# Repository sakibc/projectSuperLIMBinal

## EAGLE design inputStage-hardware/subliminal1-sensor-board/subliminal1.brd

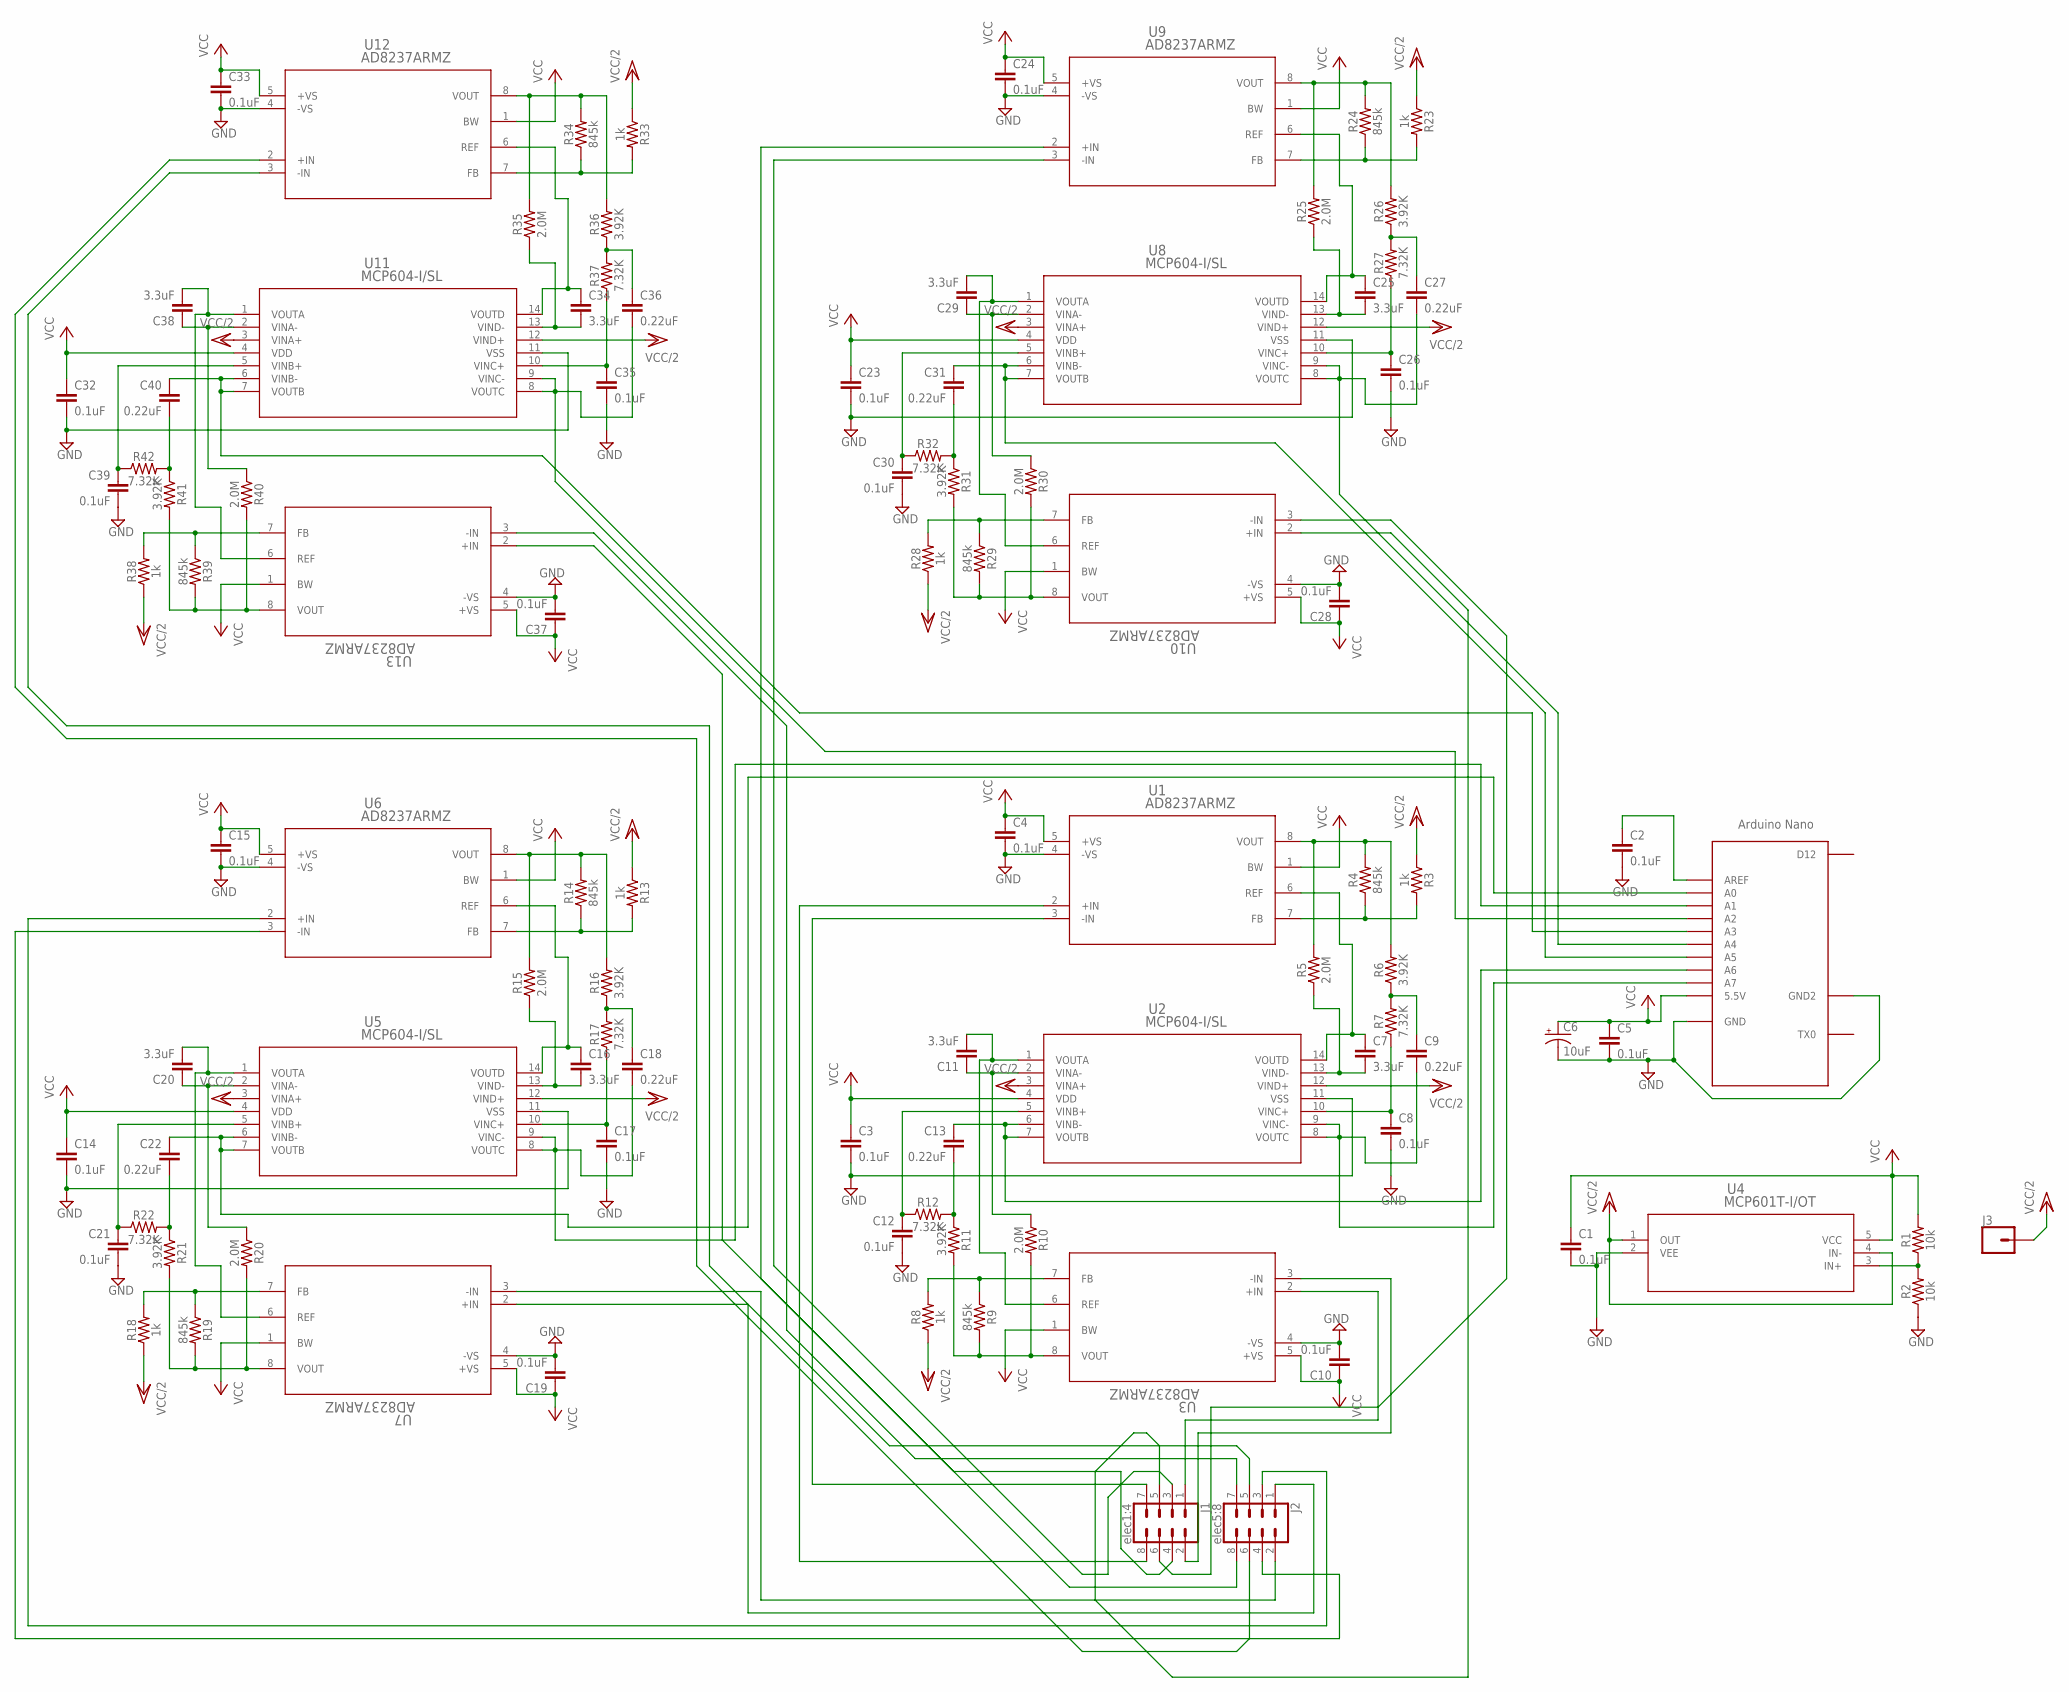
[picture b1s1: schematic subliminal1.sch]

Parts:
C1, C2, C3, C4, C5, C8, C10, C12, C14, C15, C17, C19, C21, C23, C24, C26, C28, C30, C32, C33, C35, C37, C39: 0.1uF; 0603
C6: 10uF; EIA3216
C7, C11, C16, C20, C25, C29, C34, C38: 3.3uF; 0603
C9, C13, C18, C22, C27, C31, C36, C40: 0.22uF; 0603
J1: elec1:4; 2X4
J2: elec5:8; 2X4
J3: CONN_01; 1X01
R1, R2: 10k; 0603
R3, R8, R13, R18, R23, R28, R33, R38: 1k; 0603
R4, R9, R14, R19, R24, R29, R34, R39: 845k; 0603
R5, R10, R15, R20, R25, R30, R35, R40: 2.0M; 0603
R6, R11, R16, R21, R26, R31, R36, R41: 3.92K; 0603
R7, R12, R17, R22, R27, R32, R37, R42: 7.32K; 0603
U1, U3, U6, U7, U9, U10, U12, U13: AD8237ARMZ; RM_8
U2, U5, U8, U11: MCP604-I/SL; SOIC14-N_MC
U4: MCP601T-I/OT; SOT-23-5_MC
U$1: ANALOG-NANO; ANANANOMIN

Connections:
GND: C1.2, C2.2, C3.2, C4.2, C5.2, C6.-, C8.2, C10.2, C12.2, C14.2, C15.2, C17.2, C19.2, C21.2, C23.2, C24.2, C26.2, C28.2, C30.2, C32.2, C33.2, C35.2, C37.2, C39.2, R2.1, U1.4 (-VS), U2.11 (VSS), U3.4 (-VS), U4.2 (VEE), U5.11 (VSS), U6.4 (-VS), U7.4 (-VS), U8.11 (VSS), U9.4 (-VS), U10.4 (-VS), U11.11 (VSS), U12.4 (-VS), U13.4 (-VS), U$1.GND, U$1.GND1 (GND2)
unnamed: C2.1, U$1.AREF
unnamed: R1.1, R2.2, U4.3 (IN+)
unnamed: R8.2, R9.1, U3.7 (FB)
unnamed: R9.2, R10.2, R11.2, U3.8 (VOUT)
unnamed: R4.2, R5.2, R6.2, U1.8 (VOUT)
unnamed: R3.2, R4.1, U1.7 (FB)
unnamed: C9.1, R6.1, R7.2
unnamed: C7.2, R5.1, U2.13 (VIND-)
unnamed: C7.1, U1.6 (REF), U2.14 (VOUTD)
unnamed: C8.1, R7.1, U2.10 (VINC+)
unnamed: R13.2, R14.1, U6.7 (FB)
unnamed: C13.1, U2.6 (VINB-), U2.7 (VOUTB), U$1.A6
unnamed: C11.2, U2.1 (VOUTA), U3.6 (REF)
unnamed: C13.2, R11.1, R12.2
unnamed: R14.2, R15.2, R16.2, U6.8 (VOUT)
unnamed: C16.2, R15.1, U5.13 (VIND-)
unnamed: C16.1, U5.14 (VOUTD), U6.6 (REF)
unnamed: C18.1, R16.1, R17.2
unnamed: C17.1, R17.1, U5.10 (VINC+)
unnamed: R18.2, R19.1, U7.7 (FB)
unnamed: C12.1, R12.1, U2.5 (VINB+)
unnamed: C9.2, U2.8 (VOUTC), U2.9 (VINC-), U$1.A7
unnamed: R19.2, R20.2, R21.2, U7.8 (VOUT)
unnamed: C11.1, R10.1, U2.2 (VINA-)
unnamed: C20.2, U5.1 (VOUTA), U7.6 (REF)
unnamed: C18.2, U5.8 (VOUTC), U5.9 (VINC-), U$1.A1
unnamed: C20.1, R20.1, U5.2 (VINA-)
unnamed: C22.1, U5.6 (VINB-), U5.7 (VOUTB), U$1.A0
unnamed: C22.2, R21.1, R22.2
unnamed: C21.1, R22.1, U5.5 (VINB+)
unnamed: R23.2, R24.1, U9.7 (FB)
unnamed: R24.2, R25.2, R26.2, U9.8 (VOUT)
unnamed: C25.2, R25.1, U8.13 (VIND-)
unnamed: C25.1, U8.14 (VOUTD), U9.6 (REF)
unnamed: C27.1, R26.1, R27.2
unnamed: C26.1, R27.1, U8.10 (VINC+)
unnamed: R28.2, R29.1, U10.7 (FB)
unnamed: R29.2, R30.2, R31.2, U10.8 (VOUT)
unnamed: C29.2, U8.1 (VOUTA), U10.6 (REF)
unnamed: C27.2, U8.8 (VOUTC), U8.9 (VINC-), U$1.A4
unnamed: C29.1, R30.1, U8.2 (VINA-)
unnamed: C31.1, U8.6 (VINB-), U8.7 (VOUTB), U$1.A5
unnamed: C31.2, R31.1, R32.2
unnamed: C30.1, R32.1, U8.5 (VINB+)
unnamed: R33.2, R34.1, U12.7 (FB)
unnamed: R34.2, R35.2, R36.2, U12.8 (VOUT)
unnamed: C34.2, R35.1, U11.13 (VIND-)
unnamed: C34.1, U11.14 (VOUTD), U12.6 (REF)
unnamed: C36.1, R36.1, R37.2
unnamed: C35.1, R37.1, U11.10 (VINC+)
unnamed: R38.2, R39.1, U13.7 (FB)
unnamed: R39.2, R40.2, R41.2, U13.8 (VOUT)
unnamed: C38.2, U11.1 (VOUTA), U13.6 (REF)
unnamed: C36.2, U11.8 (VOUTC), U11.9 (VINC-), U$1.A2
unnamed: C38.1, R40.1, U11.2 (VINA-)
unnamed: C40.2, R41.1, R42.2
unnamed: C39.1, R42.1, U11.5 (VINB+)
unnamed: J1.7, U1.3 (-IN)
unnamed: J1.8, U1.2 (+IN)
unnamed: J1.1, U3.2 (+IN)
unnamed: J1.4, U9.2 (+IN)
unnamed: J2.2, U7.3 (-IN)
unnamed: J2.1, U7.2 (+IN)
unnamed: J2.3, U6.2 (+IN)
unnamed: J2.4, U6.3 (-IN)
unnamed: J1.2, U3.3 (-IN)
unnamed: J1.3, U9.3 (-IN)
unnamed: J2.8, U13.2 (+IN)
unnamed: J2.7, U13.3 (-IN)
unnamed: J2.5, U12.3 (-IN)
unnamed: J2.6, U12.2 (+IN)
unnamed: J1.5, U10.2 (+IN)
unnamed: J1.6, U10.3 (-IN)
unnamed: C40.1, U11.6 (VINB-), U11.7 (VOUTB), U$1.A3
VCC: C1.1, C3.1, C4.1, C5.1, C6.+, C10.1, C14.1, C15.1, C19.1, C23.1, C24.1, C28.1, C32.1, C33.1, C37.1, R1.2, U1.1 (BW), U1.5 (+VS), U2.4 (VDD), U3.1 (BW), U3.5 (+VS), U4.5 (VCC), U5.4 (VDD), U6.1 (BW), U6.5 (+VS), U7.1 (BW), U7.5 (+VS), U8.4 (VDD), U9.1 (BW), U9.5 (+VS), U10.1 (BW), U10.5 (+VS), U11.4 (VDD), U12.1 (BW), U12.5 (+VS), U13.1 (BW), U13.5 (+VS), U$1.5V (5.5V)
VCC/2: J3.1, R3.1, R8.1, R13.1, R18.1, R23.1, R28.1, R33.1, R38.1, U2.3 (VINA+), U2.12 (VIND+), U4.1 (OUT), U4.4 (IN-), U5.3 (VINA+), U5.12 (VIND+), U8.3 (VINA+), U8.12 (VIND+), U11.3 (VINA+), U11.12 (VIND+)

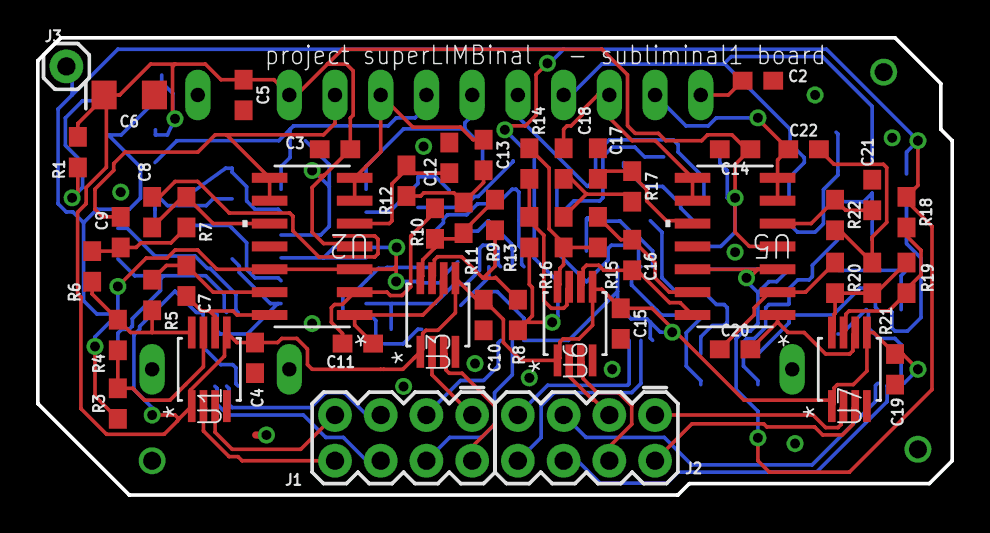
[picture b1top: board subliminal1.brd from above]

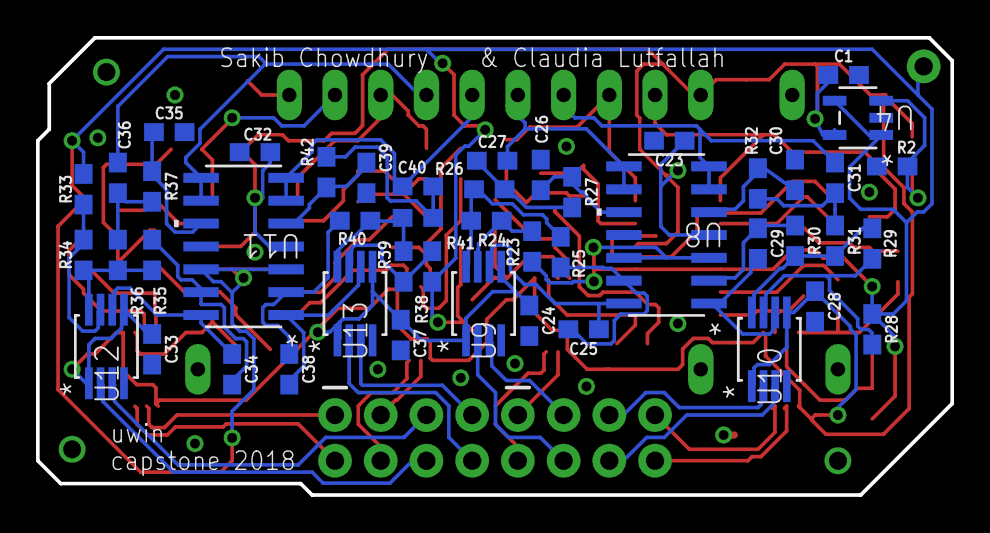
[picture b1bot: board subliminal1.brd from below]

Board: 2 copper layers, 50.8 x 25.4 mm, 99 parts (47 on the bottom side), 77 nets.

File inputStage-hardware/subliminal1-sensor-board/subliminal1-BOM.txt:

Partlist exported from /Users/sakibchowdhury/Documents/eagle/Capstone1/EMGSensorArray.sch at 2018-06-20 11:04 PM

Qty Value        Device                           Package     Parts                                                                                                       Description                                                                                                      MANUFACTURER_PART_NUMBER PROD_ID   VALUE  VENDOR            
OK1                CONN_01                          1X01        J3                                                                                                          Single connection point. Often used as Generic Header-pin footprint for 0.1 inch spaced/style header connections                                                             
OK23  0.1uF        0.1UF-0603-25V-(+80/-20%)        0603        C1, C2, C3, C4, C5, C8, C10, C12, C14, C15, C17, C19, C21, C23, C24, C26, C28, C30, C32, C33, C35, C37, C39 0.1µF ceramic capacitors                                                                                                                  CAP-00810 0.1uF                    
OK8   0.22uF       0.22UF-0603-25V-10%              0603        C9, C13, C18, C22, C27, C31, C36, C40                                                                       0.22µF ceramic capacitors                                                                                                                 CAP-07822 0.22uF                   
OK2   10k          10KOHM-0603-1/10W-1%             0603        R1, R2                                                                                                      10kΩ resistor                                                                                                                             RES-00824 10k                      
OK1   10uF         10UF-POLAR-EIA3216-16V-10%(TANT) EIA3216     C6                                                                                                          10.0µF polarized capacitors                                                                                                               CAP-00811 10uF                     
OK8   1k           1KOHM-0603-1/10W-1%              0603        R3, R8, R13, R18, R23, R28, R33, R38                                                                        1kΩ resistor                                                                                                                              RES-07856 1k                       
OK8   2.0M         2MOHMS-0603-1/10W-1%             0603        R5, R10, R15, R20, R25, R30, R35, R40                                                                       2MΩ resistor                                                                                                                              RES-10054 2.0M                     
OK8   3.3uF        3.3UF-0603-10V-10%               0603        C7, C11, C16, C20, C25, C29, C34, C38                                                                       3.3µF ceramic capacitors                                                                                                                            3.3uF                    
OK8   3.92K        3.92KOHM-0603-1/10W-1%           0603        R6, R11, R16, R21, R26, R31, R36, R41                                                                                                                                                                                                                           3.92K                    
OK8   7.32K        7.32KOHM-0603-1/10W-1%           0603        R7, R12, R17, R22, R27, R32, R37, R42                                                                                                                                                                                                                           7.32K                    
OK8   845k         845KOHM-0603-1/10W-1%            0603        R4, R9, R14, R19, R24, R29, R34, R39                                                                        845kΩ resistor                                                                                                                                      845k                     
OK8   AD8237ARMZ   AD8237ARMZ                       RM_8        U1, U3, U6, U7, U9, U10, U12, U13                                                                                                                                                                                            AD8237ARMZ                                Analog Devices Inc
OK1   ANALOG-NANO  ANALOG-NANO                      ANANANOMIN  U$1                                                                                                         Arduino Nano                                                                                                                                                                 
OK1   MCP601T-I/OT MCP601T-I/OT                     SOT-23-5_MC U4                                                                                                                                                                                                                           MCP601TIOT                                Microchip         
OK4   MCP604-I/SL  MCP604-I/SL                      SOIC14-N_MC U2, U5, U8, U11                                                                                                                                                                                                              MCP604ISL                                 Microchip         
OK1   elec1:4      CONN_04X2                        2X4         J1                                                                                                          Multi connection point. Often used as Generic Header-pin footprint for 0.1 inch spaced/style header connections                                                              
OK1   elec5:8      CONN_04X2                        2X4         J2                                                                                                          Multi connection point. Often used as Generic Header-pin footprint for 0.1 inch spaced/style header connections

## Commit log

2018-03-24 Initial commit.
2018-03-24 Added project logo to README.
2018-03-25 Set up python project for PC input.
2018-03-26 Basic PC serial data reader.
2018-04-24 Finished Arduino code for 4 ADC inputs.
2018-04-24 Added dependencies to plot serial data.
2018-04-26 Got it to graph something...
2018-04-26 Ignore dev environment settings.
2018-04-27 Added saving data to CSV file.
2018-04-28 It works, it graphs!
2018-04-28 Add defines for additional electrode numbers.
2018-04-28 Updated docstring.
2018-04-30 got it graphing 8 electrodes fast enough...
2018-05-01 fixed some problems...
2018-05-02 plot more data points each frame
2018-05-15 clean up calibration
2018-05-15 fix missing parentheses
2018-05-18 started processing data
2018-05-19 successful proof of concept and test of prediction on low-quality data
2018-05-21 made it modular
2018-05-23 restructure program for live data processing
2018-05-23 add support for ch340g on mac
2018-05-24 implemented nnmf algorithm on test signal
2018-05-25 switch over from matplotlib to pyqtgraph and add saving
2018-05-26 made the graph update cleaner
2018-05-27 successful decomposition or whatever...
2018-05-27 updated smoothing filter for live view
2018-06-19 Added Arduino codes for output stage
2018-06-19 Work on sending data to motion stage
2018-06-19 Testing filters
2018-06-19 ignore one-time calibration data
2018-06-19 Correct typo in folder name
2018-06-20 Successfully send data between PC and Arduino to move a motor
2018-06-20 successfully send some muscle information to the arduino to move a motor
2018-06-22 Added schematic, board, and gerber files for sensor board
2018-06-23 Added bill of materials for circuit board
2018-06-23 ignore SNMF library files
2018-06-23 added sparse-nmf test to decode synergy matrix unsupervised
2018-06-24 begin work on using adafruit servo shield
2018-06-25 implement control algorithm from paper
2018-06-26 package and receive multiple synergy values between pc and limb
2018-06-28 start adding headless mode that skips gui
2018-06-28 update pipfile
2018-06-28 more headless pi mode
2018-06-28 remove a head
2018-06-28 removed a head
2018-06-28 create web-server test
2018-06-28 allow remote access to web server running on pi
2018-06-29 building up webapp, shutdown functionality
2018-06-29 allow remote access to server...
2018-06-29 fix shutdown process
2018-06-29 fix "fix shutdown process"
2018-06-29 increase shutdown delay
2018-06-29 fix "fix "fix shutdown""...
2018-06-29 updated git ignore for frontend
2018-06-29 setup client-side app w/ routing and basic comms with server
2018-06-30 send connection status of sensor and motor stage
2018-07-01 start sending emg data from server to client
2018-07-03 design and plan out base frontend site
2018-07-03 silly logo loop
2018-07-08 rudimentary graph in javascript
2018-07-12 web interface fully functional
2018-07-14 updated gitignore to include website build tools
2018-07-14 shutdown failure troubleshooting
2018-07-14 attempt fix shutdown failure
2018-07-14 disable proxying in production, rollback previous changes
2018-07-14 fix syntax error
2018-07-14 fix "fix syntax error"
2018-07-14 testing something...
2018-07-15 remove brain from pineapple
2018-07-15 attempt fix uglifier
2018-07-15 fix...
2018-07-15 whatever
2018-07-15 disable uglification...
2018-07-15 disable minification...
2018-07-15 re-enable check for pi and prepare for splitting of stages
2018-07-16 Started working on improving output stage
2018-07-16 add full screen mode for website on ios
2018-07-17 add webapp manifest
2018-07-17 improve performance of sending data
2018-07-17 added test for rate of sending samples
2018-07-17 try reducing broadcast rate
2018-07-17 improve transfer performance by offloading some math to client
2018-07-18 modified output stage to test max and min pulselengths for servos
2018-07-18 make calibration more verbose and safe
2018-07-26 setup output stage
2018-07-26 Returned to only 8 electrodes
2018-07-26 fix bad monitor parameters
2018-07-26 disable combing on live data
2018-07-27 got it kinda working mostly
2018-07-27 added high-pass filter
2018-07-29 improve robustness of operation
2018-07-29 fix an import
2018-08-03 make calibration more robust
2018-08-03 fix a problem?
2018-08-03 now it actually really actually works
2020-06-06 Bump websocket-extensions in /inputStage-PC/frontend-dev
    Bumps [websocket-extensions](https://github.com/faye/websocket-extensions-node) from 0.1.3 to 0.1.4.
    - [Release notes](https://github.com/faye/websocket-extensions-node/releases)
    - [Changelog](https://github.com/faye/websocket-extensions-node/blob/master/CHANGELOG.md)
    - [Commits](https://github.com/faye/websocket-extensions-node/compare/0.1.3...0.1.4)
2020-07-17 Bump lodash from 4.17.10 to 4.17.19 in /inputStage-PC/frontend-dev
    Bumps [lodash](https://github.com/lodash/lodash) from 4.17.10 to 4.17.19.
    - [Release notes](https://github.com/lodash/lodash/releases)
    - [Commits](https://github.com/lodash/lodash/compare/4.17.10...4.17.19)
2020-07-30 Bump elliptic from 6.4.0 to 6.5.3 in /inputStage-PC/frontend-dev
    Bumps [elliptic](https://github.com/indutny/elliptic) from 6.4.0 to 6.5.3.
    - [Release notes](https://github.com/indutny/elliptic/releases)
    - [Commits](https://github.com/indutny/elliptic/compare/v6.4.0...v6.5.3)
2020-09-04 Bump lodash.mergewith from 4.6.1 to 4.6.2 in /inputStage-PC/frontend-dev
    Bumps [lodash.mergewith](https://github.com/lodash/lodash) from 4.6.1 to 4.6.2.
    - [Release notes](https://github.com/lodash/lodash/releases)
    - [Commits](https://github.com/lodash/lodash/commits)
2020-09-04 Bump node-sass from 4.9.0 to 4.13.1 in /inputStage-PC/frontend-dev
    Bumps [node-sass](https://github.com/sass/node-sass) from 4.9.0 to 4.13.1.
    - [Release notes](https://github.com/sass/node-sass/releases)
    - [Changelog](https://github.com/sass/node-sass/blob/master/CHANGELOG.md)
    - [Commits](https://github.com/sass/node-sass/compare/v4.9.0...v4.13.1)
2020-09-09 Bump http-proxy from 1.17.0 to 1.18.1 in /inputStage-PC/frontend-dev
    Bumps [http-proxy](https://github.com/http-party/node-http-proxy) from 1.17.0 to 1.18.1.
    - [Release notes](https://github.com/http-party/node-http-proxy/releases)
    - [Changelog](https://github.com/http-party/node-http-proxy/blob/master/CHANGELOG.md)
    - [Commits](https://github.com/http-party/node-http-proxy/compare/1.17.0...1.18.1)
2020-12-11 Bump ini from 1.3.5 to 1.3.7 in /inputStage-PC/frontend-dev
    Bumps [ini](https://github.com/isaacs/ini) from 1.3.5 to 1.3.7.
    - [Release notes](https://github.com/isaacs/ini/releases)
    - [Commits](https://github.com/isaacs/ini/compare/v1.3.5...v1.3.7)
2020-12-22 Bump node-notifier from 5.2.1 to 8.0.1 in /inputStage-PC/frontend-dev
    Bumps [node-notifier](https://github.com/mikaelbr/node-notifier) from 5.2.1 to 8.0.1.
    - [Release notes](https://github.com/mikaelbr/node-notifier/releases)
    - [Changelog](https://github.com/mikaelbr/node-notifier/blob/v8.0.1/CHANGELOG.md)
    - [Commits](https://github.com/mikaelbr/node-notifier/compare/v5.2.1...v8.0.1)
2021-01-05 Bump axios from 0.18.0 to 0.21.1 in /inputStage-PC/frontend-dev
    Bumps [axios](https://github.com/axios/axios) from 0.18.0 to 0.21.1.
    - [Release notes](https://github.com/axios/axios/releases)
    - [Changelog](https://github.com/axios/axios/blob/v0.21.1/CHANGELOG.md)
    - [Commits](https://github.com/axios/axios/compare/v0.18.0...v0.21.1)
2021-03-09 Bump elliptic from 6.4.0 to 6.5.4 in /inputStage-PC/frontend-dev
    Bumps [elliptic](https://github.com/indutny/elliptic) from 6.4.0 to 6.5.4.
    - [Release notes](https://github.com/indutny/elliptic/releases)
    - [Commits](https://github.com/indutny/elliptic/compare/v6.4.0...v6.5.4)
2021-03-20 Bump jinja2 from 2.10 to 2.11.3 in /inputStage-PC
    Bumps [jinja2](https://github.com/pallets/jinja) from 2.10 to 2.11.3.
    - [Release notes](https://github.com/pallets/jinja/releases)
    - [Changelog](https://github.com/pallets/jinja/blob/master/CHANGES.rst)
    - [Commits](https://github.com/pallets/jinja/compare/2.10...2.11.3)
2021-03-25 Bump pyyaml from 3.13 to 5.4 in /outputStage-PC
    Bumps [pyyaml](https://github.com/yaml/pyyaml) from 3.13 to 5.4.
    - [Release notes](https://github.com/yaml/pyyaml/releases)
    - [Changelog](https://github.com/yaml/pyyaml/blob/master/CHANGES)
    - [Commits](https://github.com/yaml/pyyaml/compare/3.13...5.4)
2021-03-30 Bump y18n from 3.2.1 to 3.2.2 in /inputStage-PC/frontend-dev
    Bumps [y18n](https://github.com/yargs/y18n) from 3.2.1 to 3.2.2.
    - [Release notes](https://github.com/yargs/y18n/releases)
    - [Changelog](https://github.com/yargs/y18n/blob/master/CHANGELOG.md)
    - [Commits](https://github.com/yargs/y18n/commits)
2021-05-07 Bump url-parse from 1.4.1 to 1.4.7 in /inputStage-PC/frontend-dev
    Bumps [url-parse](https://github.com/unshiftio/url-parse) from 1.4.1 to 1.4.7.
    - [Release notes](https://github.com/unshiftio/url-parse/releases)
    - [Commits](https://github.com/unshiftio/url-parse/compare/1.4.1...1.4.7)
2021-05-08 Bump eventlet from 0.23.0 to 0.31.0 in /inputStage-PC
    Bumps [eventlet](https://github.com/eventlet/eventlet) from 0.23.0 to 0.31.0.
    - [Release notes](https://github.com/eventlet/eventlet/releases)
    - [Changelog](https://github.com/eventlet/eventlet/blob/master/NEWS)
    - [Commits](https://github.com/eventlet/eventlet/compare/v0.23.0...v0.31.0)
2021-05-09 Bump lodash from 4.17.10 to 4.17.21 in /inputStage-PC/frontend-dev
    Bumps [lodash](https://github.com/lodash/lodash) from 4.17.10 to 4.17.21.
    - [Release notes](https://github.com/lodash/lodash/releases)
    - [Commits](https://github.com/lodash/lodash/compare/4.17.10...4.17.21)
2021-05-10 Bump hosted-git-info from 2.6.1 to 2.8.9 in /inputStage-PC/frontend-dev
    Bumps [hosted-git-info](https://github.com/npm/hosted-git-info) from 2.6.1 to 2.8.9.
    - [Release notes](https://github.com/npm/hosted-git-info/releases)
    - [Changelog](https://github.com/npm/hosted-git-info/blob/v2.8.9/CHANGELOG.md)
    - [Commits](https://github.com/npm/hosted-git-info/compare/v2.6.1...v2.8.9)
2021-05-27 Bump dns-packet from 1.3.1 to 1.3.4 in /inputStage-PC/frontend-dev
    Bumps [dns-packet](https://github.com/mafintosh/dns-packet) from 1.3.1 to 1.3.4.
    - [Release notes](https://github.com/mafintosh/dns-packet/releases)
    - [Changelog](https://github.com/mafintosh/dns-packet/blob/master/CHANGELOG.md)
    - [Commits](https://github.com/mafintosh/dns-packet/compare/v1.3.1...v1.3.4)
2021-06-01 Bump urllib3 from 1.23 to 1.26.5 in /outputStage-PC
    Bumps [urllib3](https://github.com/urllib3/urllib3) from 1.23 to 1.26.5.
    - [Release notes](https://github.com/urllib3/urllib3/releases)
    - [Changelog](https://github.com/urllib3/urllib3/blob/main/CHANGES.rst)
    - [Commits](https://github.com/urllib3/urllib3/compare/1.23...1.26.5)
    ---
    updated-dependencies:

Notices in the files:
parts and their libraries:
SparkFun-Capacitors: Licensing: Creative Commons ShareAlike 4.0 International - https://creativecommons.org/licenses/by-sa/4.0
